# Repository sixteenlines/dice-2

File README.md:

# Würfel 2.0

Projekt ESP8266 - D1 mini Matrix-Würfel mit Webserver

Umfasst eine LED Matrix, 3 Taster (davon 2 frei programmierbar) und eine einfache Website, welche leicht mit Funktionen erweitert werden kann.
Eine Möglichkeit ist der Tausch der serienmäßig verbauten 9V Batterie mit einem 3.7V Lithium Akku. Für dieses [Upgrade](#lithium-akku-upgrade) ist die Platine bereits vorbereitet.

## Repo Übersicht

### cad

Beinhaltet KiCad Projektdaten - Schaltplan und Platinenlayout.

### data

Beinhaltet Files für das Dateisystem

-   HTML Seiten
-   CSS Stylesheets
-   Icons und Bilder
-   Textdateien
    -   creds (SSID, Passwort, etc)
    -   settings (Timeoutzeiten)

### src

Quellcode

-   header_main.hpp - Macros und Header
-   main.cpp - Microcontroller Programmroutinen

## IDE & Framework

Das Projekt wurde in der [PlatformIO](https://marketplace.visualstudio.com/items?itemName=platformio.platformio-ide) Entwicklungsumgebung und mithilfe des Arduino Frameworks in Visual Studio Code realisiert. Die Erweiterung bezieht automatisch alle benötigten Libraries, welche in der [platformio.ini](https://github.com/sixteenlines/dice-2/blob/production/platformio.ini) hinterlegt sind.

In dieser werden auch die Einstellungen für den seriellen Monitor oder die entsprechenden Flags für den Programmer gesetzt.

## Dokumentation

### Einschalten

Das Einschalten des Geräts erfolgt mit dem linken Taster.

Der Controller versorgt sich über eine [Selbsthaltefunktion](https://github.com/sixteenlines/dice-2/blob/production/self-retain.jpg?raw=true) und schaltet so nach einiger Zeit (einstellbar über Webinterface) automatisch ab.

Ein manueller Reset ist über den Reset pin auf der Unterseite des Gehäuses möglich.

### AP-Mode

Beim Einschalten versucht der Controller sich mit den bekannten Daten in einem bestehendem WLAN als Client anzumelden. Misslingt dies nach 3 Versuchen, leuchtet ein roter Punkt in der Matrix auf und der Controller schaltet wieder ab.

Um die Anmeldedaten zu bearbeiten, kann das Gerät im Wifi-Manager-Modus gestartet werden. Hierzu wird beim Einschalten der mittlere Taster 5 Sekunden lang gedrückt gehalten. Der ESP hostet nun einen Access-Point und wird sichtbar als "MAGIC-DICE-SETUP".

Bei der Verbindung versucht der Controller DNS Anfragen auf ein Captive Portal umzuleiten um die Eingabemaske automatisch aufzurufen. Gelingt dies nicht, kann der Wifi-Manager über die [8.8.8.8](8.8.8.8) erreicht werden.

Nach Absenden des Formulars startet der Controller neu, bei erfolgreicher Verbindung im WLAN leuchtet ein grüner Punkt in der Matrix auf.

### Client-Mode

Wurde im Formular eine statische IP vergeben, kann man das Webinterface unter der eingestellten IP erreichen.

Wird DHCP verwendet kann die erhaltene IP über die [serielle Schnittstelle](#serielle-schnittstelle) ausgelesen werden.

Es kann nun über Betätigen des linken Tasters oder den Button im Webinterface gewürfelt werden.

Ebenso ist im Webinterface die Matrix als <div> Container widergespiegelt. Unter der Matrix kann die Farbe zum Würfeln eingestellt werden. Außerdem können individuelle LEDs angeklickt werden um sie in der gewählten Farbe aufleuchten zu lassen. Wiederholtes klicken schaltet sie wieder aus.

Über das Einstellungsmenü kann die Dauer der Beleuchtung und die Zeit bis der Controller abschaltet, konfiguriert werden.

Ebenso findet sich hier der WiFi-Manager wieder, falls in ein anderes Netzwerk gewechselt werden soll. Nach Eingabe muss jedoch der Controller erst [neu gestartet](#einschalten) werden.

### Offline-Mode

Wird beim Einschalten der rechte Taster bis zum Aufleuchten eines blauen Punktes gehalten, startet das Gerät im Offline-Modus. Hierbei wird das Wifi-Modul abgeschaltet um die Akkulaufzeit erheblich zu erhöhen. In diesem Modus ist jedoch lediglich die Würfel-Funktion verfügbar.

### Serielle Schnittstelle

Verbindet man das Gerät über USB, können mithilfe eines Terminalprogramms Debugging-Informationen und von DHCP erhaltene IP-Adressen ausgelesen werden.

Der Controller sendet standardmäßig mit einer Baudrate von 115200.

Zur Fehlerdiagnose ist ratsam, den Controller zu verbinden, die entsprechende serielle Schnittstelle zu öffnen und zunächst einen [reset](#einschalten) durchzuführen.

Es werden nun sämtliche Schritte des Bootvorgangs gespiegelt. Außerdem werden Anfragen an den Webserver gelogt.

## Lithium Akku Upgrade

### Übersicht und Stückliste

Um das Gerät mit einem wiederaufladbarem Akku auszustatten müssen einige zusätzliche Teile bezogen werden. In Klammern jeweils aufgeführt, ist der verwendete Footprint auf der Platine oder eine Teileempfehlung.

1x 2.0 USB-C Port (GCT-USB4085)

1x 3.7V Lithium Akku (LiPo 103450 - 51mm x 39mm x 10mm)

1x LiPo Laderegler mit DC-DC Converter 3.7V - 5V

1x Drahtbrücke (0.6mm)

1x Klebestreifen für Akku ([iFixit Klebestreifen](https://store.ifixit.de/products/stretch-release-battery-adhesive))

Optional:

1x JST-PH2 Header oder JST-XH2 oder JST-EH2 je nach Akku/Hersteller (siehe Datenblatt)

Die bereits verbaute Steckleiste J1 ist ausgelegt auf ein [kompaktes Modul](https://de.aliexpress.com/item/33034500618.html) mit DC-DC Wandler und Laderegler. Wird von diesem abgewichen, ist auf eine [korrekte Pinbelegung](https://github.com/sixteenlines/dice-2/blob/production/cad/screenshot/dcdc_charge_header.jpg?raw=true) nach Schaltplan zu achten. Auch ist die korrekte Polarität beim direkten Verlöten der Akku Litzen, oder Bestücken des JST-Headers zu prüfen.

### Arbeitsschritte:

1. Öffnen des Gehäuses (Schraubendreher) und Entfernen der 9V Blockbatterie (Seitenschneider)

2. Entfernen des TSR1-2450 (U2)

3. Bestücken und Verlöten von Drahtbrücke B1 (Pin 1 - Pin 3 von U2)

4. Bestücken und Verlöten von THT 2.0 USB Connector

5. Bestücken und Verlöten des optionalen JST-Headers oder verlöten der Akku Litzen

6. Aufsetzen und Verlöten des DCDC-Charge Controller Moduls

7. USB Ladegerät anschließen und verifizieren, dass die Charge LED des eingesetzten Moduls aufleuchtet.

8. Akku mit Klebestreifen an die Stelle der alten 9V Batterie verkleben und Gehäuse wieder schließen.

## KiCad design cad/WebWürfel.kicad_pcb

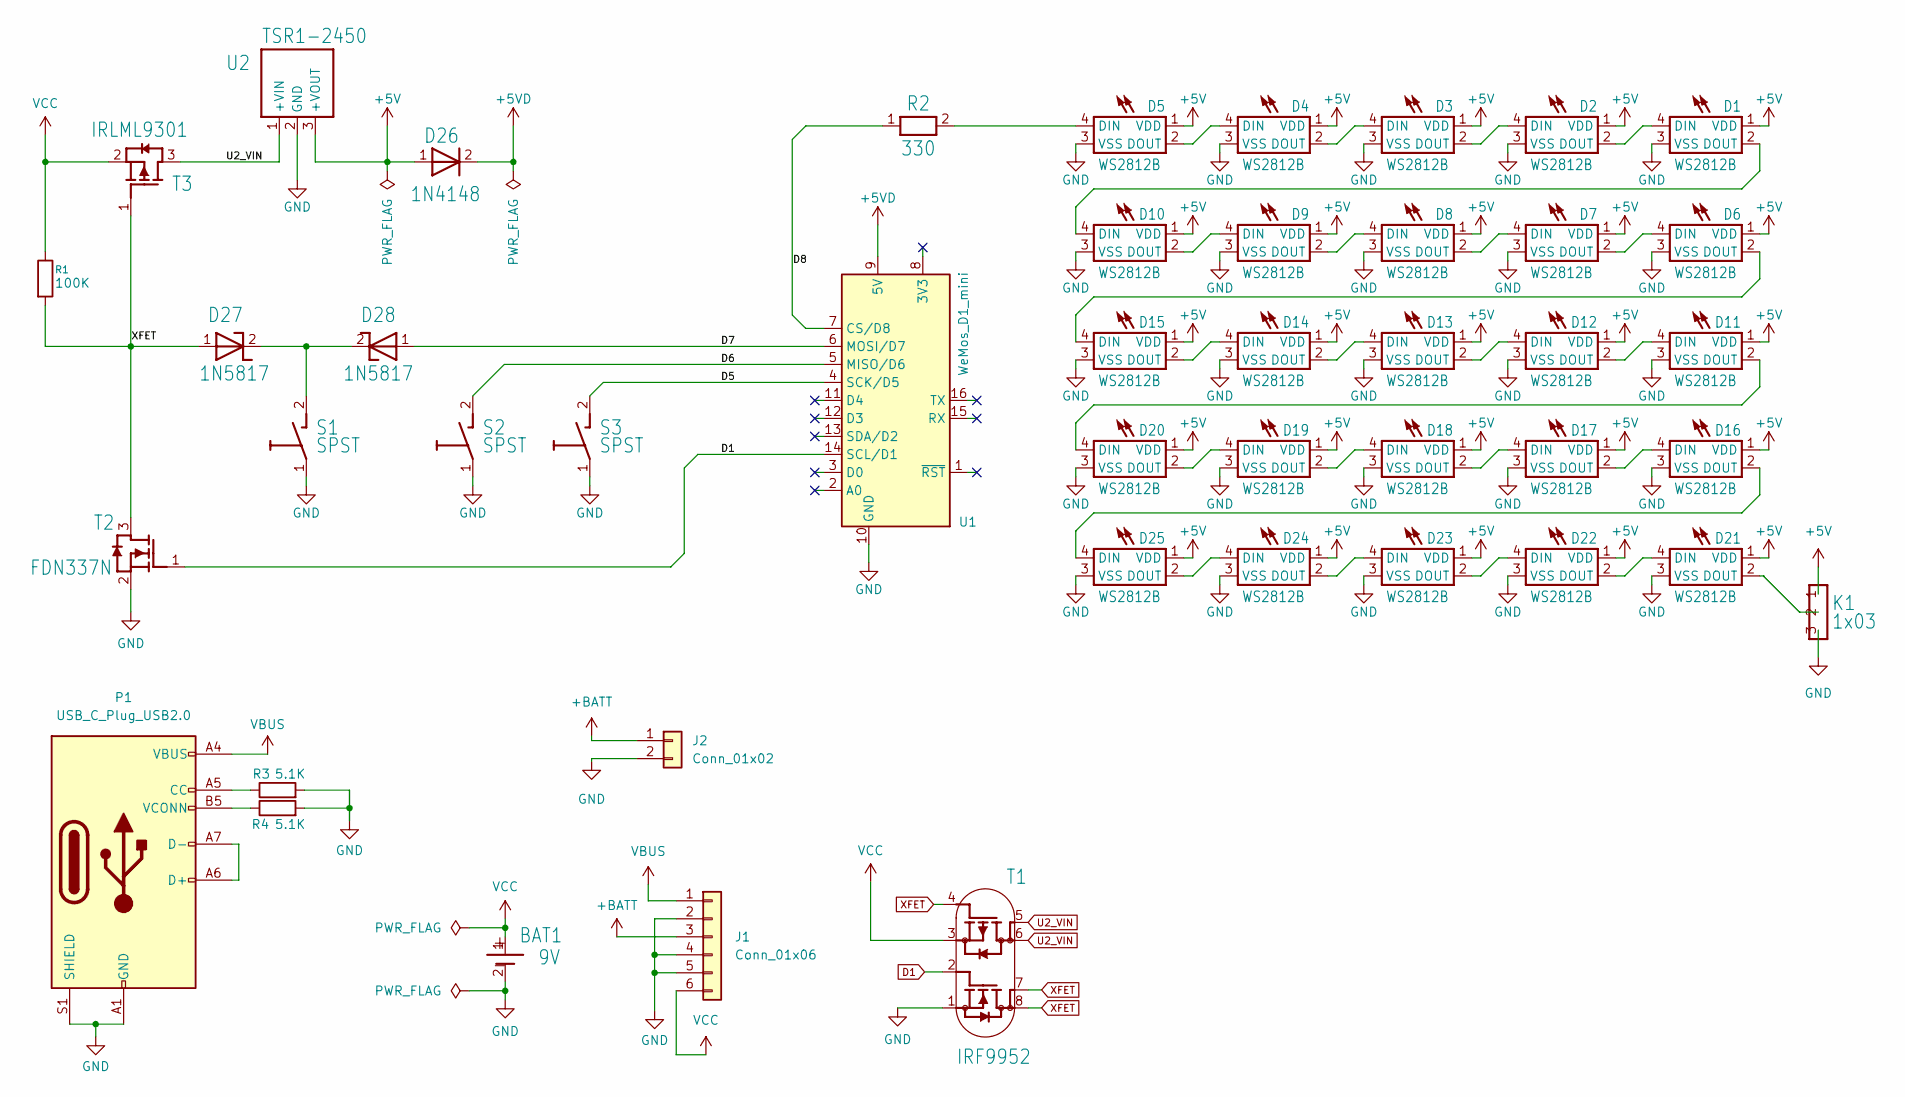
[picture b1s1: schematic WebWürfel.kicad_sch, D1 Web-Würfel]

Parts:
BAT1: 9V; BATTERIE_2
D1, D2, D3, D4, D5, D6, D7, D8, D9, D10, D11, D12, D13, D14, D15, D16, D17, D18, D19, D20, D21, D22, D23, D24, D25: WS2812B; WS2812B_9
D26: 1N4148; DO35_1
D27: 1N5817; DO41_40
D28: 1N5817; DO41_41
J1: Conn_01x06; PinHeader_1x06_P2.54mm_Vertical
J2: Conn_01x02; JST_PH_B2B-PH-K_1x02_P2.00mm_Vertical
K1: 1x03; 1X03_BUCHSE_8
P1: USB_C_Plug_USB2.0; USB_C_Receptacle_GCT_USB4085
R1: 100K; R_1206_3216Metric
R2: 330; 0207_44
R3, R4: 5.1K; R_1206_3216Metric
S1, S2, S3: SPST; 1254.1017_DRUCKTASTER_34
T1: IRF9952; SO8_SOT96-1_39
T2: FDN337N; SOT-23_3_42
T3: IRLML9301; SOT-23_3_43
U1: WeMos_D1_mini; WEMOS_D1_mini_light
U2: TSR1-2450; TRACO-TSR1-24_0

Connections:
+5V: D1.1 (VDD), D2.1 (VDD), D3.1 (VDD), D4.1 (VDD), D5.1 (VDD), D6.1 (VDD), D7.1 (VDD), D8.1 (VDD), D9.1 (VDD), D10.1 (VDD), D11.1 (VDD), D12.1 (VDD), D13.1 (VDD), D14.1 (VDD), D15.1 (VDD), D16.1 (VDD), D17.1 (VDD), D18.1 (VDD), D19.1 (VDD), D20.1 (VDD), D21.1 (VDD), D22.1 (VDD), D23.1 (VDD), D24.1 (VDD), D25.1 (VDD), D26.1, K1.1, U2.3 (+VOUT)
+5VD: D26.2, U1.9 (5V)
+BATT: J1.3 (BAT), J2.1
/D5: S3.2, U1.4 (SCK/D5)
/D6: S2.2, U1.5 (MISO/D6)
/D7: D28.1, U1.6 (MOSI/D7)
/D8: R2.1, U1.7 (CS/D8)
D1: T1.2, T2.1, U1.14 (SCL/D1)
GND: BAT1.2, D1.3 (VSS), D2.3 (VSS), D3.3 (VSS), D4.3 (VSS), D5.3 (VSS), D6.3 (VSS), D7.3 (VSS), D8.3 (VSS), D9.3 (VSS), D10.3 (VSS), D11.3 (VSS), D12.3 (VSS), D13.3 (VSS), D14.3 (VSS), D15.3 (VSS), D16.3 (VSS), D17.3 (VSS), D18.3 (VSS), D19.3 (VSS), D20.3 (VSS), D21.3 (VSS), D22.3 (VSS), D23.3 (VSS), D24.3 (VSS), D25.3 (VSS), J1.2 (GND), J1.4 (GND), J1.5 (GND), J2.2, K1.3, P1.A1 (GND), P1.A12 (GND), P1.B1 (GND), P1.B12 (GND), P1.S1 (SHIELD), R3.2, R4.2, S1.1, S2.1, S3.1, T1.1, T2.2, U1.10 (GND), U2.2 (GND)
unnamed: D1.4 (DIN), D2.2 (DOUT)
unnamed: D1.2 (DOUT), D10.4 (DIN)
unnamed: D2.4 (DIN), D3.2 (DOUT)
unnamed: D3.4 (DIN), D4.2 (DOUT)
unnamed: D4.4 (DIN), D5.2 (DOUT)
unnamed: D5.4 (DIN), R2.2
unnamed: D6.4 (DIN), D7.2 (DOUT)
unnamed: D7.4 (DIN), D8.2 (DOUT)
unnamed: D8.4 (DIN), D9.2 (DOUT)
unnamed: D9.4 (DIN), D10.2 (DOUT)
unnamed: D11.4 (DIN), D12.2 (DOUT)
unnamed: D11.2 (DOUT), D20.4 (DIN)
unnamed: D12.4 (DIN), D13.2 (DOUT)
unnamed: D13.4 (DIN), D14.2 (DOUT)
unnamed: D14.4 (DIN), D15.2 (DOUT)
unnamed: D6.2 (DOUT), D15.4 (DIN)
unnamed: D16.4 (DIN), D17.2 (DOUT)
unnamed: D16.2 (DOUT), D25.4 (DIN)
unnamed: D17.4 (DIN), D18.2 (DOUT)
unnamed: D18.4 (DIN), D19.2 (DOUT)
unnamed: D19.4 (DIN), D20.2 (DOUT)
unnamed: D21.4 (DIN), D22.2 (DOUT)
unnamed: D21.2 (DOUT), K1.2
unnamed: D22.4 (DIN), D23.2 (DOUT)
unnamed: D23.4 (DIN), D24.2 (DOUT)
unnamed: D24.4 (DIN), D25.2 (DOUT)
unnamed: D27.2, D28.2, S1.2
unnamed: P1.A5 (CC), R3.1
unnamed: P1.A6 (D+), P1.A7 (D-)
unnamed: P1.B5 (VCONN), R4.1
U2_VIN: T1.5, T1.6, T3.3, U2.1 (+VIN)
VBUS: J1.1 (VIN), P1.A4 (VBUS), P1.A9 (VBUS), P1.B4 (VBUS), P1.B9 (VBUS)
VCC: BAT1.1, J1.6 (VOUT), R1.1, T1.3, T3.2
XFET: D27.1, R1.2, T1.4, T1.7, T1.8, T2.3, T3.1

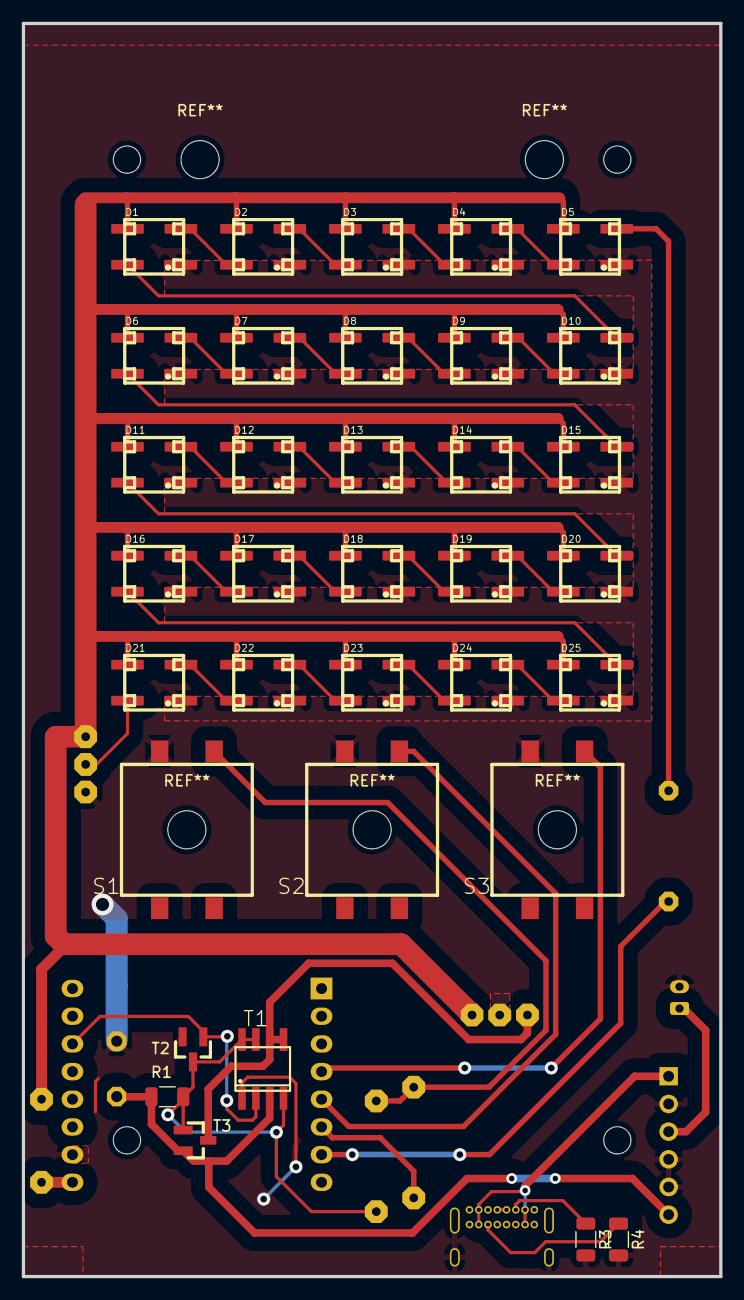
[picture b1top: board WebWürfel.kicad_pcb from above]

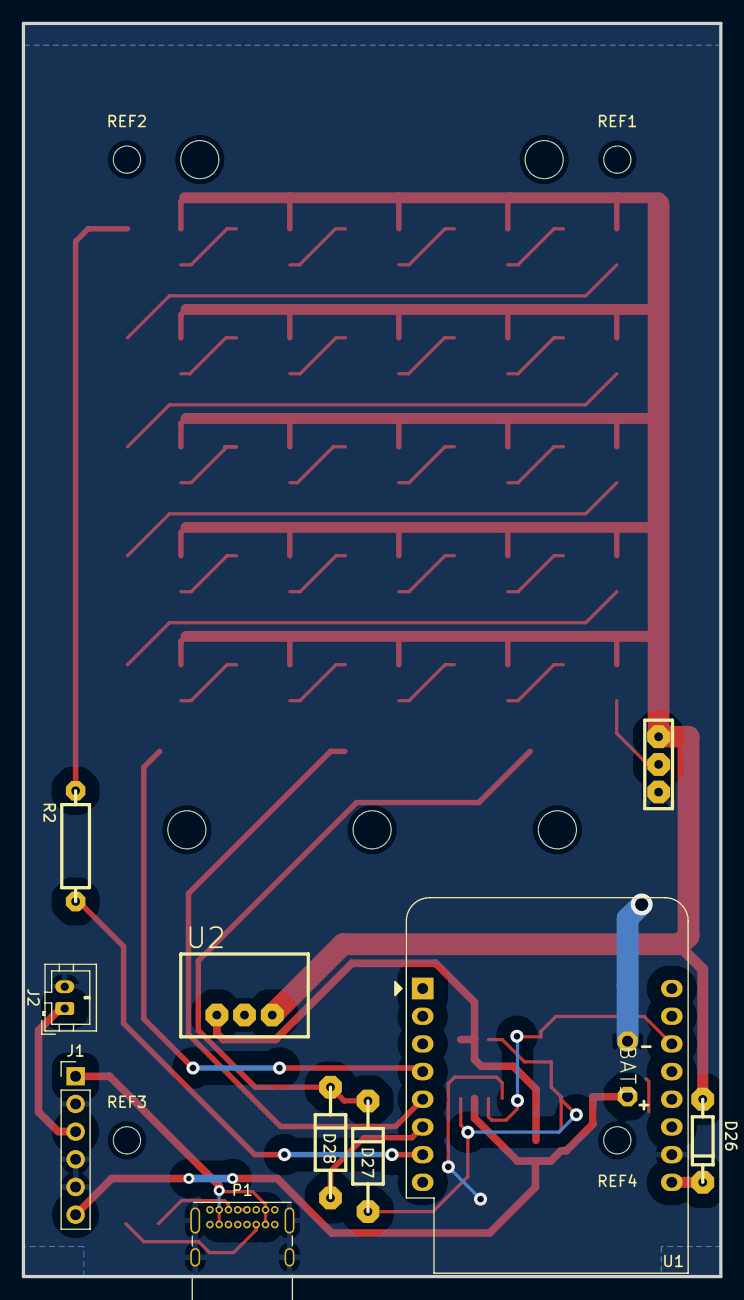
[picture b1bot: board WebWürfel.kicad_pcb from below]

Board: 2 copper layers, 64.0 x 115.0 mm, 49 parts (15 on the bottom side), 43 nets.

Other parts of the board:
REF1, REF2, REF3, REF4: MountingHole_2.5mm

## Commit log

2023-05-26 trying to figure out eeprom
2023-05-27 Individual LED switching support TEST
2023-05-27 deep sleep moved to main loop to prevent crashing
2023-05-29 Change to ESP_EEPROM lib for efficiency
2023-05-31 Nothing works
2023-05-31 What have i done
2023-06-01 working manager no css
2023-06-01 not working manager but css
2023-06-01 Seems to work now, time to break it again
2023-06-02 Breadboard broke?
2023-06-02 not working led lags
2023-06-02 Happy loading leds
2023-06-05 Changed neopixel to grb for board layout
2023-06-05 Changed value communication from get to post
2023-06-05 Led number position adjusted for final layout
2023-06-05 minor tweaks
2023-06-05 minor tweaks 2
2023-06-06 reordered functions and implemented LED objects
2023-06-06 removed serialprint for performance
2023-06-06 updated pinout for production pcb
2023-06-06 updated pinout for debug breadboard
2023-06-06 updated led color profile
2023-06-06 btn layout correction
2023-06-06 cleaned up led functions
2023-06-06 Settings page first demo
2023-06-07 Added settings to webpage
2023-06-07 fixes for webpage and handling of settings
2023-06-20 settings sync working + safari href fix
2023-06-20 improved password visibility toggle
2023-06-20 viewport adjusted for ap manager
2023-06-20 wiped static ip
2023-06-27 improved comments up to hostManager()
2023-06-29 minor fixes and added comments
2023-06-29 Reintroduced serial debug messages
2023-07-18 fixed accidental removal of file write
2023-07-20 adding kicad files
2023-07-20 updated gitignore
2023-07-20 First readme draft, to be continued
2023-07-20 typo fix
2023-07-21 readme proofreading
2023-07-21 further proofreading
2023-09-08 updated cad
2023-09-13 changed buttons to internal pullups
2023-09-14 old led grid
2023-09-15 rotated d1 mini by 90°
2023-09-18 restructured code into seperate files
2023-09-18 fixed vars and added offline mode
2023-09-18 die roll glitch fix
2023-09-18 half brightness leds for longer battery life
2023-09-18 roll delay slider beta
2023-10-05 kicad update battery
2023-10-06 LiPo Anleitung
2023-10-06 readme fix
